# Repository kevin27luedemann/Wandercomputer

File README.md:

# Wandercomputer

Wandercomputer is the follow up of the Fahradcomputer project.
It includes code from the stopwatch project because of its superior coding.

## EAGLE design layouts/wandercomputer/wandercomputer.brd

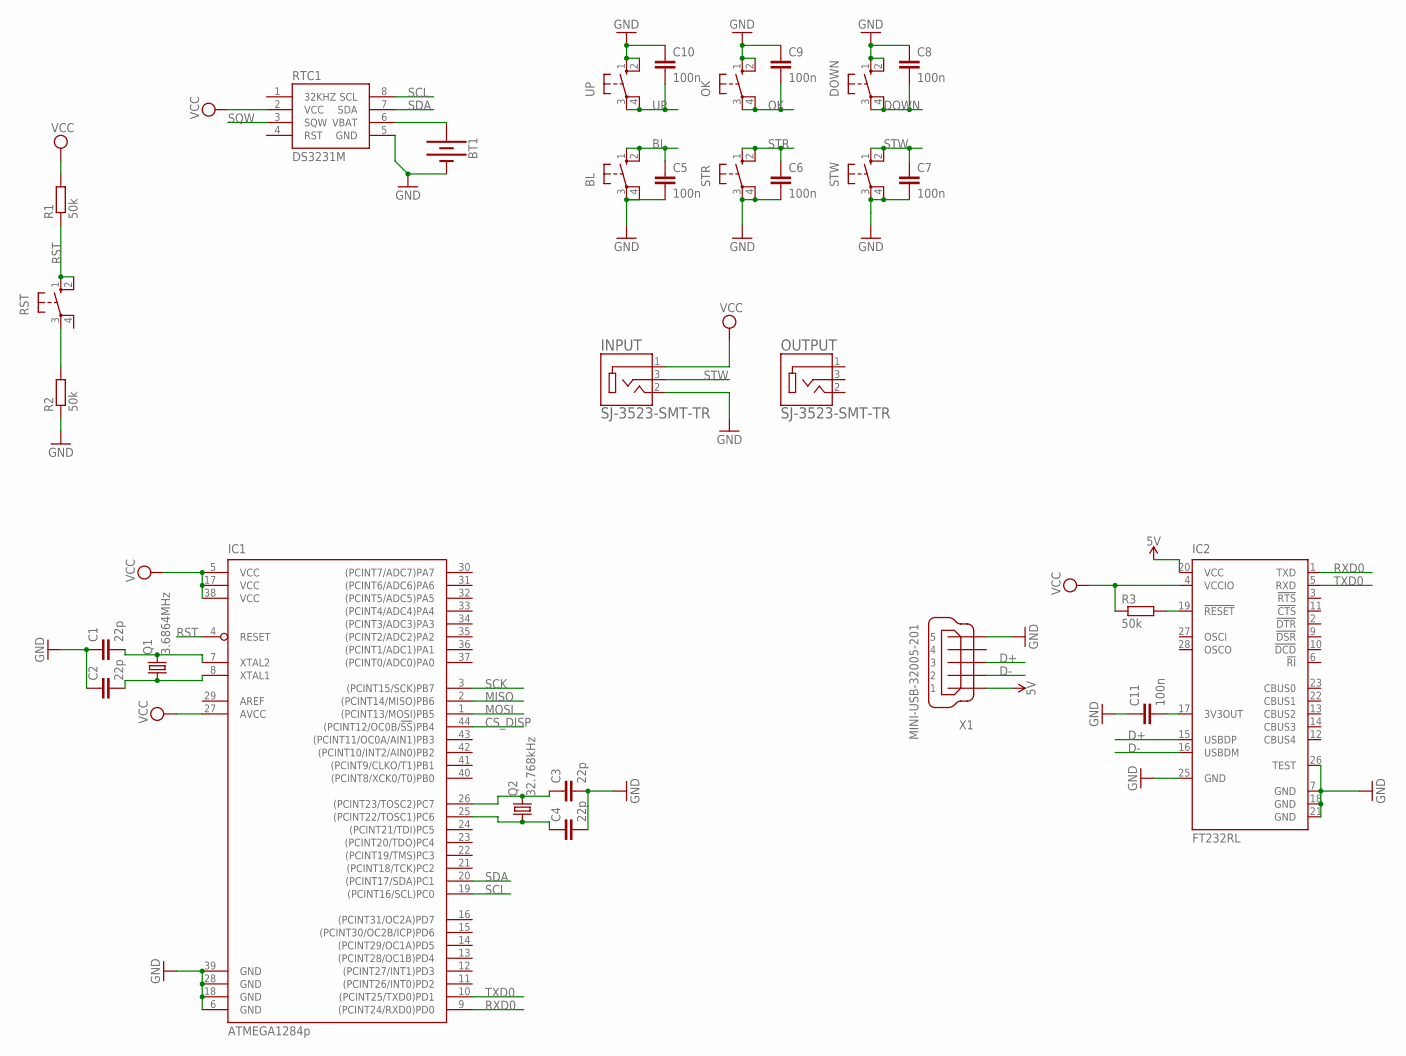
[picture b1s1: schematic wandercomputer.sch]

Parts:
BL: 10-XX; B3F-10XX
BT1: BATTERY-20MM_SMD; BATTCON_20MM
C1, C2, C3, C4: 22p; C1808
C5, C6, C7, C8, C9, C10, C11: 100n; C1808
DOWN: 10-XX; B3F-10XX
IC1: ATMEGA1284p; TQFP44
IC2: FT232RL; SSOP28
INPUT: SJ-3523-SMT-TR; CUI_SJ-3523-SMT-TR
OK: 10-XX; B3F-10XX
OUTPUT: SJ-3523-SMT-TR; CUI_SJ-3523-SMT-TR
Q1: 3.6864MHz; HC49U70
Q2: 32.768kHz; TC26V
R1, R2, R3: 50k; R3216
RST: 10-XX; B3F-10XX
RTC1: DS3231M; SO08
STR: 10-XX; B3F-10XX
STW: 10-XX; B3F-10XX
UP: 10-XX; B3F-10XX
X1: MINI-USB-32005-201; 32005-201

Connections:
5V: IC2.20 (VCC), X1.1
BL: BL.1 (S), BL.2 (S1), C5.1
CS_DISP: IC1.44 ((PCINT12/OC0B/!SS!)PB4)
D+: IC2.15 (USBDP), X1.3
D-: IC2.16 (USBDM), X1.2
DOWN: C8.2, DOWN.3, DOWN.4 (P1)
GND: BL.3, BL.4 (P1), BT1.2 (-), C1.1, C2.1, C3.2, C4.2, C5.2, C6.2, C7.2, C8.1, C9.1, C10.1, C11.1, DOWN.1 (S), DOWN.2 (S1), IC1.6 (GND), IC1.18 (GND), IC1.28 (GND), IC1.39 (GND), IC2.7 (GND), IC2.18 (GND), IC2.21 (GND), IC2.25 (GND), IC2.26 (TEST), INPUT.2, OK.1 (S), OK.2 (S1), R2.1, RTC1.5 (GND), STR.3, STR.4 (P1), STW.3, STW.4 (P1), UP.1 (S), UP.2 (S1), X1.5
MISO: IC1.2 ((PCINT14/MISO)PB6)
MOSI: IC1.1 ((PCINT13/MOSI)PB5)
unnamed: C3.1, IC1.26 ((PCINT23/TOSC2)PC7), Q2.2
unnamed: C4.1, IC1.25 ((PCINT22/TOSC1)PC6), Q2.1
unnamed: R2.2, RST.3
unnamed: C1.2, IC1.7 (XTAL2), Q1.2
unnamed: C2.2, IC1.8 (XTAL1), Q1.1
unnamed: C11.2, IC2.17 (3V3OUT)
unnamed: IC2.19 (!RESET), R3.2
unnamed: BT1.1 (+), RTC1.6 (VBAT)
OK: C9.2, OK.3, OK.4 (P1)
RST: IC1.4 (RESET), R1.1, RST.1 (S), RST.2 (S1)
RXD0: IC1.9 ((PCINT24/RXD0)PD0), IC2.1 (TXD)
SCK: IC1.3 ((PCINT15/SCK)PB7)
SCL: IC1.19 ((PCINT16/SCL)PC0), RTC1.8 (SCL)
SDA: IC1.20 ((PCINT17/SDA)PC1), RTC1.7 (SDA)
SQW: RTC1.3 (SQW)
STR: C6.1, STR.1 (S), STR.2 (S1)
STW: C7.1, INPUT.3, STW.1 (S), STW.2 (S1)
TXD0: IC1.10 ((PCINT25/TXD0)PD1), IC2.5 (RXD)
UP: C10.2, UP.3, UP.4 (P1)
VCC: IC1.5 (VCC), IC1.17 (VCC), IC1.27 (AVCC), IC1.38 (VCC), IC2.4 (VCCIO), INPUT.1, R1.2, R3.1, RTC1.2 (VCC)

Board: 2 copper layers, 30 parts (0 on the bottom side), 24 nets, no tracks yet.

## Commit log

2018-08-19 initial Layout

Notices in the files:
parts and their libraries:
SparkFun-Clocks: Licensing: Creative Commons ShareAlike 4.0 International - https://creativecommons.org/licenses/by-sa/4.0
